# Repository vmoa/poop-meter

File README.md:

# poop-meter

Source code and design for the ultrasnoic septic tank monitor and main water shutoff.

* Doc: Documentation and technical notes.
* Deprecated Arduino and Perl code for the previous incarnation.
* Poop-Valve: Schematic for the water main shutoff valve.
* etc: Support files (Raspberry Pi startup script, crontab).
* src: Python source code.

## TL;DR

Tracks the depth of the effluent in the septic holding tank. Notifies a human (SMS text)
at intervals, more frequently as the tank gets more full.  Shuts off the main water valve
if the tank gets to a panic level.

## Notable Notes

Software dependencies are spelled out in `poopWatcher.py`, but we also need a confguration file
that tells us how to authenticate with Twilio to send text messages.  This file can reside `twilio.conf`
tin any of the curerent directory, in './etc/twilio.conf', or in '/usr/local/etc/twilio.conf'.  For
security reasons this file is not in the repository.  Create the file and fill out at least the
`[twilio]` stanza and add users to the `recipient` stanza as desired.

```
[twilio]
account_sid = **********************************
auth_token  = ********************************
from_phone = +1xxxyyyzzzz

[recipient]
dave = +1xxxyyyzzzz
```

A more detailed explanation is forthcoming.

## Detailed Design

Super high level: we are multi-threaded and are a mix between polled and GPIO event driven threads.
A side effect of this is that software bugs do not generally cause fatal errors.  Polling is handled
by `poop.Poop.perSecond()` which, first thing, schedules itself to run again in one second.  It then,
as prescribed by the `poopinterval` dictionary, dispatches an ADC sample of the poop tank, flashes the
heartbeat LED, prints a status report to the log, does housekeeping, and (regarless of the dictionary)
decides if we need to page a human and/or open/close the mains valve.

Simple, no?

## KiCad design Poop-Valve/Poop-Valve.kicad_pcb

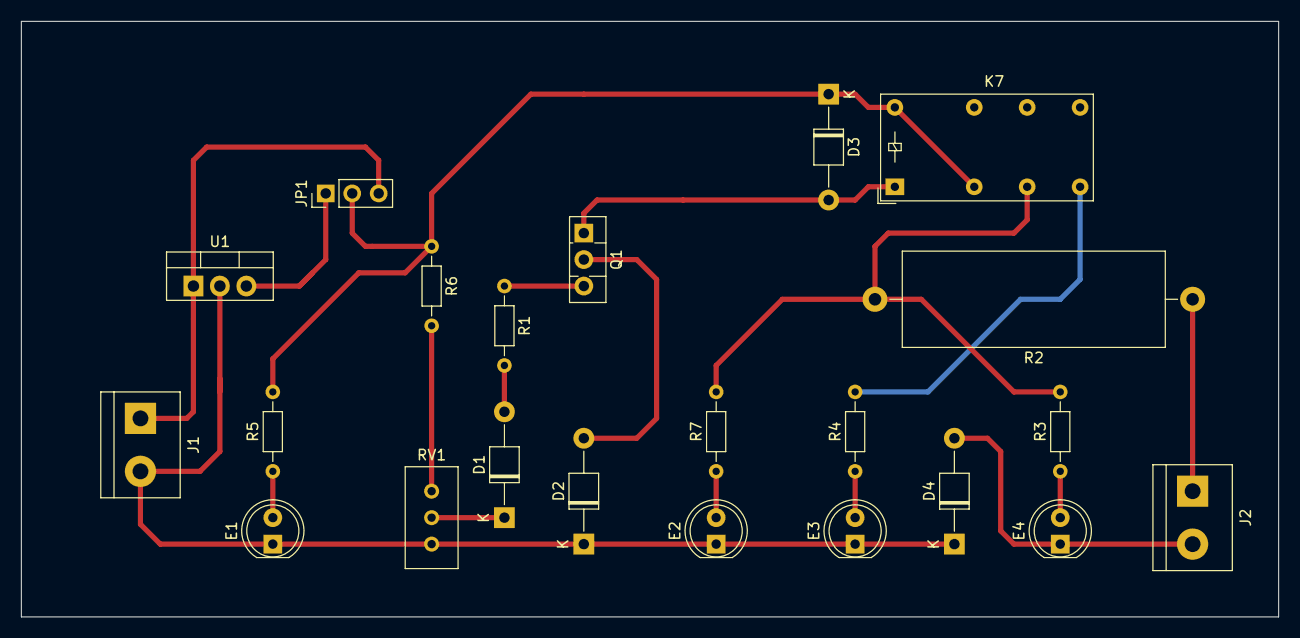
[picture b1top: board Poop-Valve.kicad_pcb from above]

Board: 2 copper layers, 120.7 x 57.1 mm, 22 parts (0 on the bottom side), 18 nets.

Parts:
D1: 1N4732A; D_T-1_P10.16mm_Horizontal
D2, D3, D4: 1N4007; D_T-1_P10.16mm_Horizontal
E1: Power; LED_D5.0mm
E2: Charging; LED_D5.0mm
E3: Charged; LED_D5.0mm
E4: B.Conn; LED_D5.0mm
J1: 18VDC; TerminalBlock_bornier-2_P5.08mm
J2: Battery; TerminalBlock_bornier-2_P5.08mm
JP1: Run/Cal; PinHeader_1x03_P2.54mm_Vertical
K7: SPDT Relay; Relay_DPDT_Finder_30.22
Q1: D882; TO-126-3_Vertical
R1, R3: 1000; R_Axial_DIN0204_L3.6mm_D1.6mm_P7.62mm_Horizontal
R2: 1Ω/5W; R_Axial_Power_L25.0mm_W9.0mm_P30.48mm
R4, R5: 1500; R_Axial_DIN0204_L3.6mm_D1.6mm_P7.62mm_Horizontal
R6: 10K; R_Axial_DIN0204_L3.6mm_D1.6mm_P7.62mm_Horizontal
R7: 1200; R_Axial_DIN0204_L3.6mm_D1.6mm_P7.62mm_Horizontal
RV1: 50K; Potentiometer_Bourns_3386C_Horizontal
U1: LM7815; TO-220-3_Vertical

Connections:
GND: D2.1, D4.1, E1.1, E2.1, E3.1, J1.2, RV1.3, U1.2
unnamed: D1.1, RV1.2
unnamed: D1.2, R1.2
unnamed: D2.2, Q1.2
unnamed: D3.1, JP1.2, K7.4, K7.12, R5.2, R6.1
unnamed: D3.2, K7.1, Q1.1
unnamed: D4.2, E4.1, J2.2
unnamed: E1.2, R5.1
unnamed: E2.2, R7.1
unnamed: E3.2, R4.1
unnamed: E4.2, R3.1
unnamed: J1.1, JP1.3, U1.1
unnamed: J2.1, R2.1
unnamed: JP1.1, U1.3
unnamed: K7.3, R2.2, R3.2, R7.2
unnamed: K7.5, R4.2
unnamed: Q1.3, R1.1
unnamed: R6.2, RV1.1

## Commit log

2018-03-02 twonked
2018-04-18 Initial revision
2018-04-24 Added EEPROM support; finished adding button routines
2018-04-24 Clenaed up indentation; moved globals to top; removed extranous code
2018-05-02 added EEPROM support to retain data during reboot or power failure
2018-05-04 Version 1.1 Detect when sensor is unplugged and don't track hi/low water marks Add a version entry to the menu system
2018-09-22 v1.2 (plus): updated numbers; added curPool to menu
2018-09-22 v1.4: updated empty/full based on dipping
2018-09-27 restored POOP_EMPTY to 420
2021-11-30 added pager logic
2021-11-30 fixed logging
2021-12-01 fixed device logic; fixed scoping issue with lastPct; log more page detail
2021-12-22 parse input more robustly; track/report abs
2021-12-22 enable virtual chomp
2022-09-23 moved things aroud
2022-09-23 explained directory structure
2022-09-23 added docs
2022-09-23 add schematic PDF
2022-09-24 v0.2 changed relay configuration
2022-09-27 v0.3 pivot to maual override relay
2022-09-27 cleaned up some lables
2022-10-02 v0.4 fix override logic; detect override; resize A4->US
2022-10-02 renamed poopMonitor.py -> poopWatcher.py
2022-10-02 ignore local config files
2022-10-02 started on Python port
2022-10-02 added class files
2022-10-02 add __pycache__
2022-10-02 completed gpio and valve open/close logic
2022-10-03 add paging goodies
2022-10-03 hardware layout diagram
2022-10-04 beefed out arduino class
2022-10-04 cleaned up pager logic
2022-10-07 add adc.py
2022-10-09 update groups comment
2022-10-20 v0.5 add connectors
2022-10-20 v0.6 fix led connector pinout
2022-10-29 checkpoint to change computers
2022-10-29 add ultrasonic sensor datasheet
2022-10-29 add README.md
2022-10-29 fix pdf link
2022-10-29 use actual cs pin we wired; add differentailChannel() method
2022-11-06 notify about manual override mode
2022-11-06 add simulator mode
2022-11-12 checkpoint: add adc averaging
2022-11-12 add stub for `notify()` method
2022-11-13 get_{value,voltage}() return average over <num_samples>
2022-11-13 add adc device; printStatus() includes adc
2022-11-30 move into subdir
2022-12-05 Added Grove LCD support
2022-12-05 Moved grove update to class method updatePoop()
2023-01-13 ignore kicad dregs
2023-01-13 v0.7 correct ADC sample wiring
2023-01-29 v0.8 reconfigure manual override; updated layout for clarity
2023-02-02 v0.9 add override shunt and sense transistors
2023-02-02 v0.10 add Master Override switch
2023-03-04 added logging and locking
2023-03-04 added locking to perSecond
2023-03-04 added comment about system needs
2023-03-13 added do_sample(); added unit test
2023-03-13 first stab at business logic to open/close valve
2023-03-13 first stab at business logic for incremental paging
2023-03-13 removed unused arduino include
2023-03-18 added class Valve; fixed open/close logic
2023-03-18 return floats/ints as appropriate; enhanced unit testing
2023-03-18 fixed message format; moved poopmap
2023-03-18 handle override notifications
2023-03-18 pass args.simulate into device.Gpio()
2023-03-18 created class Poop; moved Override.check() into Valve.maybeOperate()
2023-03-18 bumped version to v0.9.1
2023-03-18 add vavle state to poop message
2023-03-18 fix initialization logic; add setColor()
2023-03-18 move lcd into device
2023-03-18 version v0.9.2
2023-03-19 refactored poop logic into several files (poop.py, valve.py, override.py) instead of device.py
2023-03-19 version v0.9.3
2023-03-19 moved poop_notify() and poopmap into poop.py
2023-03-19 move simulate logic into each module
2023-03-19 include reboot notice in first page
2023-03-19 add lcd.latentMessage() so bootup message does not have to block
2023-03-19 update LCD color based on poop level
2023-03-19 handle valve stuck midway
2023-03-19 updated program name
2023-03-19 version v0.9.4
2023-03-19 clean up startup commandy stuff
2023-03-20 increase status interval to 60 seconds
2023-03-20 ignore more KiCad drivel
2023-03-20 v0.11 reconfigure 3.3v override relay drive
2023-03-20 v1.0 promote final draft to production
2023-03-20 promote latest beta to v1.0
2023-03-20 start a timer to update the display shortly after restart
2023-03-20 reference code for Grove LCD
2023-03-20 reference code for MCP3xxx ADC
2023-03-20 moved from src
2023-03-20 descirbe legacy code
2023-03-20 refactored source tree
2023-03-20 paths now refelect refactored source
2023-03-20 bump version to v1.0.2
2023-03-20 cleaned up installation instructions
2023-03-20 added crontab
2023-03-20 moved to legacy
2023-03-27 disengage direction relay after operation
2023-03-27 update status every second if in simulate mode
2023-04-19 v1.1 replace valve connector
2023-04-20 added grove.service to reset Grove LCD before starting poop.service
2023-04-20 bumped version to 1.0.3
2023-04-20 now v1.0.3 for reals
2023-04-21 add symlink to VERSION
2023-04-21 add WorkingDirectory
2023-04-21 add support for `nopage` sentinel; Pull version from first line of VERSION file
2023-04-21 bump version to v1.0.4rc0
2023-04-21 moved grove init functionality into poop.service
2023-04-21 bumped version to v1.0.4rc1
2023-04-22 send command args to grove if specified
2023-04-22 reset grove on Stop operation with (un)happy message
2023-04-22 bumped version to v1.0.4rc2
2023-04-24 v1.2 reconfigure override relay to use 5V voltage divider; renumber parts; miscellaneous cosmetic cleanups
2023-04-28 added first pass at override mode
2023-04-28 cleaned up override mode detection
2023-04-28 add module specific debugging
2023-04-28 convert NotifyXxx into interval[]; finish (I hope) implementing override `mode`
2023-04-28 distinguish between startTime and modeStartTime
2023-04-28 set color `indigo` in override; toggle indigo/red when `URGENT` and `override`
2023-04-30 cleaned up (or added) override notifications
2023-04-30 moved LCD update into updateDisplay() and fixed override flashing
2023-04-30 check override mode (instead of just override button) on valve closure; cancel SOFT override when level reaches PANIC
2023-04-30 bumped version to v1.0.4rc3
2023-04-30 calibrate threshold based on bench testing
2023-04-30 reformat version on lcd so release candidates can fit
2023-04-30 bumped version to v1.0.4
2023-05-01 added some jpgs
2023-05-01 renamed
2023-05-01 updated REAMDE to show current structure; add links to schematic and pic
2023-05-06 added and documented multiple Twilio configs
2023-05-14 added RRD support
2023-05-14 cleaned up doc
2023-05-14 twiddle with the RRD file
2023-05-14 ignore rrd png test files
2023-05-14 bumped version ot 1.0.5rc0
2023-05-14 woops! left debugging rrd timing in place
2023-05-14 bumped version to v1.0.5rc1
2023-05-14 report age of last rrd update
2023-05-14 update `nominal` value from last pump out
2023-05-14 calcuate percent based on `empty` and `full` (but still linear)
2023-05-14 bumped version to v1.0.5rc2
2023-05-14 replace linear percent calculation with a step function to simulalte a cylindrical top of tank
2023-05-14 bumped version to v1.0.5rc3
2023-05-21 fixed level colors; added rudimentrary command args
2023-05-28 use epoch time instead of free format; add command line args
2023-05-28 batch insert data instead of one at a time
2023-05-28 tune `closed` to track MAX instead of LAST value; add command args
2023-05-28 added valve; dramatically prettified graph; added legend; parse command args
2023-05-28 bumped version to v1.0.5rc4
2023-05-28 immediately call updateRrd on valve `opened` or `closed` transitioning high
2023-05-28 bumped version to v1.0.5
2023-05-28 whoops! crontab entries should set start time (-s) not end time (-d)
2023-09-29 version v1.0.5rc0
2023-09-29 add open/close sentinel file support
2023-09-29 bumped version to v1.0.6rc0
2023-09-29 made check_sentinel_files a classmethod; fixed some boffos
2023-09-29 bumped version to v1.0.6rc1
